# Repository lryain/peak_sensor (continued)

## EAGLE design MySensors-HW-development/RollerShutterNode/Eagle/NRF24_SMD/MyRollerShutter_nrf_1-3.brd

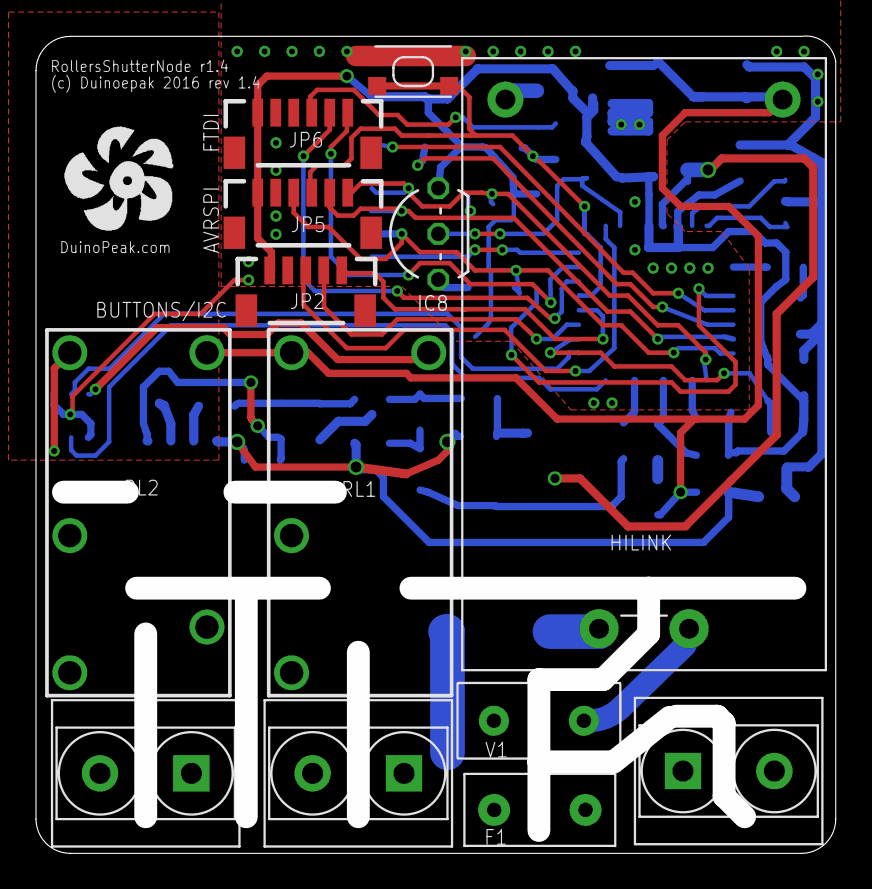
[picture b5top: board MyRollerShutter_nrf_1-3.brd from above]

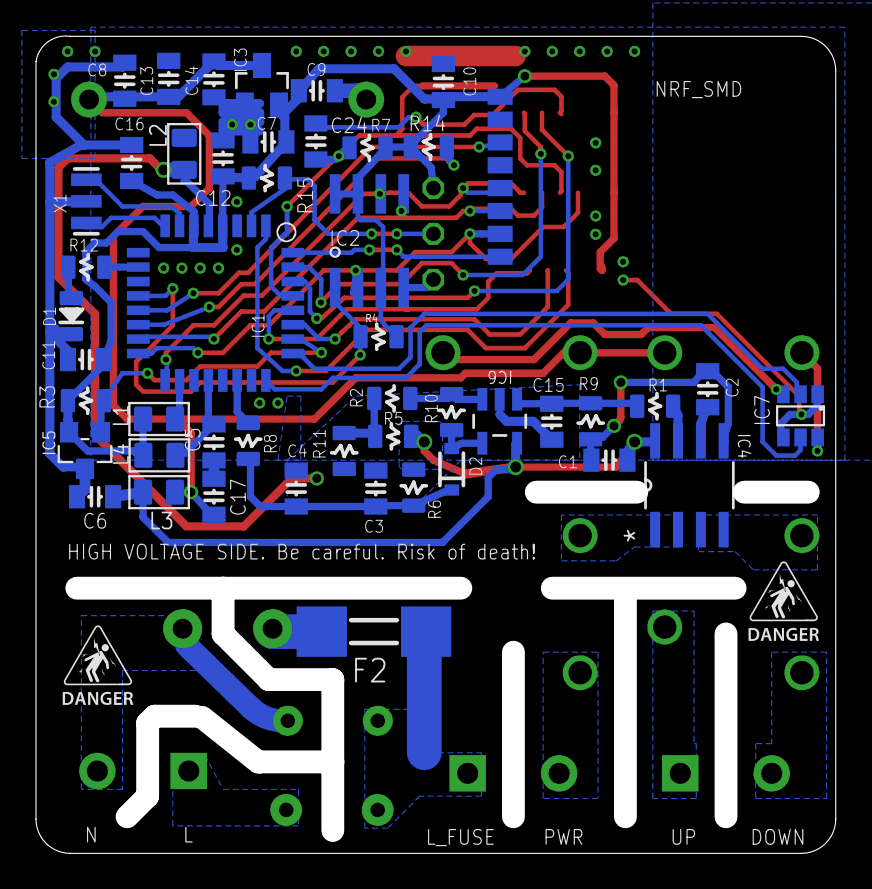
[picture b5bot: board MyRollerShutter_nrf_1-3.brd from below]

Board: 2 copper layers, 44.4 x 45.4 mm, 64 parts (50 on the bottom side), 48 nets.

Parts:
C1: 0.1uf; 0805-CAP
C2, C6, C17: 10n; 0805-CAP
C3, C10, C13: 4u7; 0805-CAP
C4, C5, C7, C11, C12, C14, C16: 0.1u; 0805-CAP
C8: 1u; 0805-CAP
C9: 10u; 0805-CAP
C15: DNP; 0805-CAP
C24: 100n; 0805-CAP
D1: LED0805; 0805-LED
D2: 1n916 type..; SOD-323
F1: FUSE_BEL_RST5_5A
F2: FUSE_MF2410; 2410
HILINK: HILINK_HLK-PM01
IC1: ATMega-328; TQFP32-08
IC2: AT25DF512C-SSHN-B; SO-08
IC3: MCP1703CB; SOT23
IC4: ACS712_5A; SOIC127P600X175-8N
IC5: ATSHA204A; SOT23
IC6: LM321; SOT95P285X120-5N
IC7: MDC3105DMT1
IC8: DS1820; TO92-
J1, J2, J3: SCREW-TERMINAL-2P-3470110P1; 2P-5.0
JP2: 1X05-1MM
JP5, JP6: 1X06-1MM
L1, L2, L3, L4: or 0ohms; L0805
NRF_SMD: NRF24L01+SMD_MODULE
R1, R2, R7, R8, R9, R15: 10k; 0805-RES
R3, R14: 56k; 0805-RES
R4: 0805-RES
R5: 4.7k; 0805-RES
R6: 100k; 0805-RES
R10: 47k; 0805-RES
R11: 2k; 0805-RES
R12: 1k5; 0805-RES
RL1: G5Q-1A-5VDC; G5Q_SINGLE
RL2: G5Q-1-EU-5VDC; RELAY-G5Q
SW1: SPST_TACT-KMR2; KMR2
U$2, U$3: ELECTROCUTION_SMALL
U$4: DUINOFUN-LOGO-PCB-0.8
V1: VARISTOR_B72207S251K101
X1: 8 MHz; RESONATOR-SMD

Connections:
5V: C8.1, C13.1, C14.1, C17.1, HILINK.V+, IC3.3, L4.2, RL1.1, RL2.5
12_220: J1.2, RL1.3
A3: IC1.26, IC5.1, R3.1
A4_SDA: IC1.27, JP2.2
A5_SCL: IC1.28, JP2.1
A6_ADC: C3.1, C4.2, D2.1, R6.2, R8.2
A7: IC1.22, R8.1
AGND: C1.2, C2.2, C3.2, C4.1, C15.2, IC1.5, IC4.5, IC6.2, L2.2, R6.1, R9.1, R11.1
AREF: C5.1, IC1.20, L3.1
D0_RX: IC1.30, JP6.5
D1_TX: IC1.31, JP6.6
D2: IC1.32, NRF_SMD.IRQ
D3: IC1.1, JP2.3
D4: IC1.2, IC8.2, R15.2
D9: IC1.13, NRF_SMD.CE
DTR: C24.1, JP6.4
FLASH_CSN: IC1.12, IC2.1, R4.1
GND: C5.2, C6.2, C7.2, C8.2, C9.2, C10.1, C11.2, C12.2, C13.2, C14.2, C16.2, C17.2, D1.MINUS, HILINK.V-, IC1.3, IC1.21, IC2.4, IC3.1, IC5.3, IC7.GND1, IC7.GND2, IC8.1, JP2.4, JP5.2, JP6.2, JP6.3, L2.1, NRF_SMD.GND, SW1.1, SW1.3, X1.2
IN_ACS: IC4.1, IC4.2, RL1.2
L: F1.1, J2.1
LED: IC1.10, R12.1
LM_OUT: D2.2, IC6.4, R10.2
MISO: IC1.16, IC2.2, JP5.3, NRF_SMD.MISO
MOSI: IC1.15, IC2.5, JP5.5, NRF_SMD.MOSI
M_DOWN: J3.2, RL2.3
M_UP: J3.1, RL2.4
N: HILINK.AC2, J2.2, V1.1
unnamed: C2.1, IC4.6
unnamed: IC4.7, R1.1
unnamed: IC1.18, L1.2
unnamed: IC7.VOUT2, RL1.5
unnamed: F2.2, HILINK.AC1
unnamed: C15.1, IC6.1, R1.2, R9.2
unnamed: IC6.3, R2.1, R10.1
unnamed: IC1.7, X1.1
unnamed: D1.PLUS, R12.2
unnamed: R2.2, R5.1, R11.2
unnamed: IC7.VOUT1, RL2.1
unnamed: IC1.8, X1.3
OUT_ACS: IC4.3, IC4.4, RL2.2
PHASE: F1.2, F2.1, J1.1, V1.2
REL_DOWN: IC1.25, IC7.VIN2
REL_UP: IC1.24, IC7.VIN1
RF_CSN: IC1.14, R14.1
RST: C24.2, IC1.29, JP5.4, R7.2, SW1.2, SW1.4
SCK: IC1.17, IC2.6, JP5.6, NRF_SMD.SCK
VCC: C7.1, C9.1, C10.2, C11.1, C12.1, C16.1, IC1.4, IC1.6, IC2.3, IC2.7, IC2.8, IC3.2, IC5.2, IC8.3, JP2.5, JP5.1, JP6.1, L1.1, L3.2, NRF_SMD.3V, R3.2, R4.2, R7.1, R14.2, R15.1
VCC_ACS: C1.1, C6.1, IC4.8, IC6.5, L4.1, R5.2
